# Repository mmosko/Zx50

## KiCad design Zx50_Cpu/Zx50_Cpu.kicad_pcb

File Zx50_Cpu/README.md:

# Zx50 CPU Card

## 1. Overview
This is the primary CPU board for the Zx50 8-slot passive backplane system. It hosts the Z80 microprocessor (running at 8 to 10 MHz) and acts as the master controller for the primary bus. 

Crucially, this board is designed to coexist with the **Zx50 Shadow Bus** architecture. It features a hardware-level "firewall" that allows a coprocessor (like a Pi Pico on the Bus Probe or Front Panel card) to request the bus via `~BUSRQ`. When the Z80 yields (`~BUSAK`), the CPU card instantly severs itself from the backplane, allowing the Pico to perform high-speed 40MHz DMA transfers without electrical contention.

## 2. Core Architecture & Logic Families

### The CPU
* **Z80 Microprocessor:** Zilog `Z84C00xxP` CMOS variant in a 40-pin DIP package. 

### The Transceiver Firewall (`74AHCT245`)
To drive the heavy capacitance of the 8-slot backplane, standard `74HC` logic is insufficient. This board uses **`74AHCT245`** octal bus transceivers (±8mA drive current) for all bus interfacing. 
To optimize PCB trace routing, a unified BOM of four '245s is used (rather than mixing in '244s). 
* **Convention:** "A-Ports" face the Z80; "B-Ports" face the Backplane.
* **Address Bus (x2):** `DIR` is hardwired to `+5V` (A -> B only).
* **Control Bus (x1):** `DIR` is hardwired to `+5V` (A -> B only). *(Note: The unused `A8` input on this buffer is tied to GND via a 10kΩ pull-up to prevent CMOS floating-gate oscillation).*
* **Data Bus (x1):** `DIR` is dynamically driven directly by the Z80's `~RD` pin. 
* **Isolation (`~OE`):** The `~OE` pins of all four transceivers are driven by an inverted `~BUSAK` signal. 

### Glue Logic (`74AHC1G14`)
A single "Little Logic" SOT-23-5 Schmitt-Trigger Inverter (`SN74AHC1G14DBVR` / Digi-Key: `296-1088-1-ND`) is used to invert the Z80's `~BUSAK` signal to correctly drive the active-low `~OE` pins of the transceiver wall.

## 3. Power-On Reset (POR) Subsystem
The Master Reset logic is completely handled by a **Microchip `MCP1318MT-46LE/OT`** Supervisor IC (SOT-23-5, Digi-Key: `MCP1318MT-46LE/OTCT-ND`). 

* **The Boot Delay:** It imposes a strict ~200ms delay on power-up. This guarantees the 1000µF backplane bulk capacitance is fully charged, the clock oscillators are stable, and the Pi Pico bootloaders on the peripheral cards have fully initialized before the Z80 takes its first step.
* **Voltage Threshold:** Trips at 4.6V to prevent brown-out corruption.
* **Open-Drain Output:** Safely shares the backplane's `~RESET` line with other cards that may pull the line low.
* **No Watchdog:** The `1318M` specifically omits the hardware watchdog timer (unlike the 1316M), preventing accidental Z80 reboots during extended Pi Pico DMA operations.
* **Local Button:** A right-angle tactile switch (`Omron B3F` / Digi-Key: `SW402-ND`) is wired to the `~MR` (Manual Reset) pin, providing perfect, capacitor-free hardware debouncing for bench testing.

## 4. Interfaces

* **J1 - Backplane:** Standard Zx50 80-pin Edge Connector.
* **J3 - Clock Mezzanine (2x5 Socket):** Receives `MCLK` (40MHz), `CLK` (10MHz ZCLK), and manages the async-latched `~STEP` signals from the Zx50 Clock Mezzanine module.
* **J4 - Front Panel (2x5 Header):** Mirrors the signals sent to the system Front Panel. Includes `RUN`, `~STEP`, `~RESET`, and `TX`/`RX` paths. The `~STEP` signal is routed down to the backplane's `AUX` pin (Pin 80) to coordinate with the Clock Mezzanine and Bus Probe.

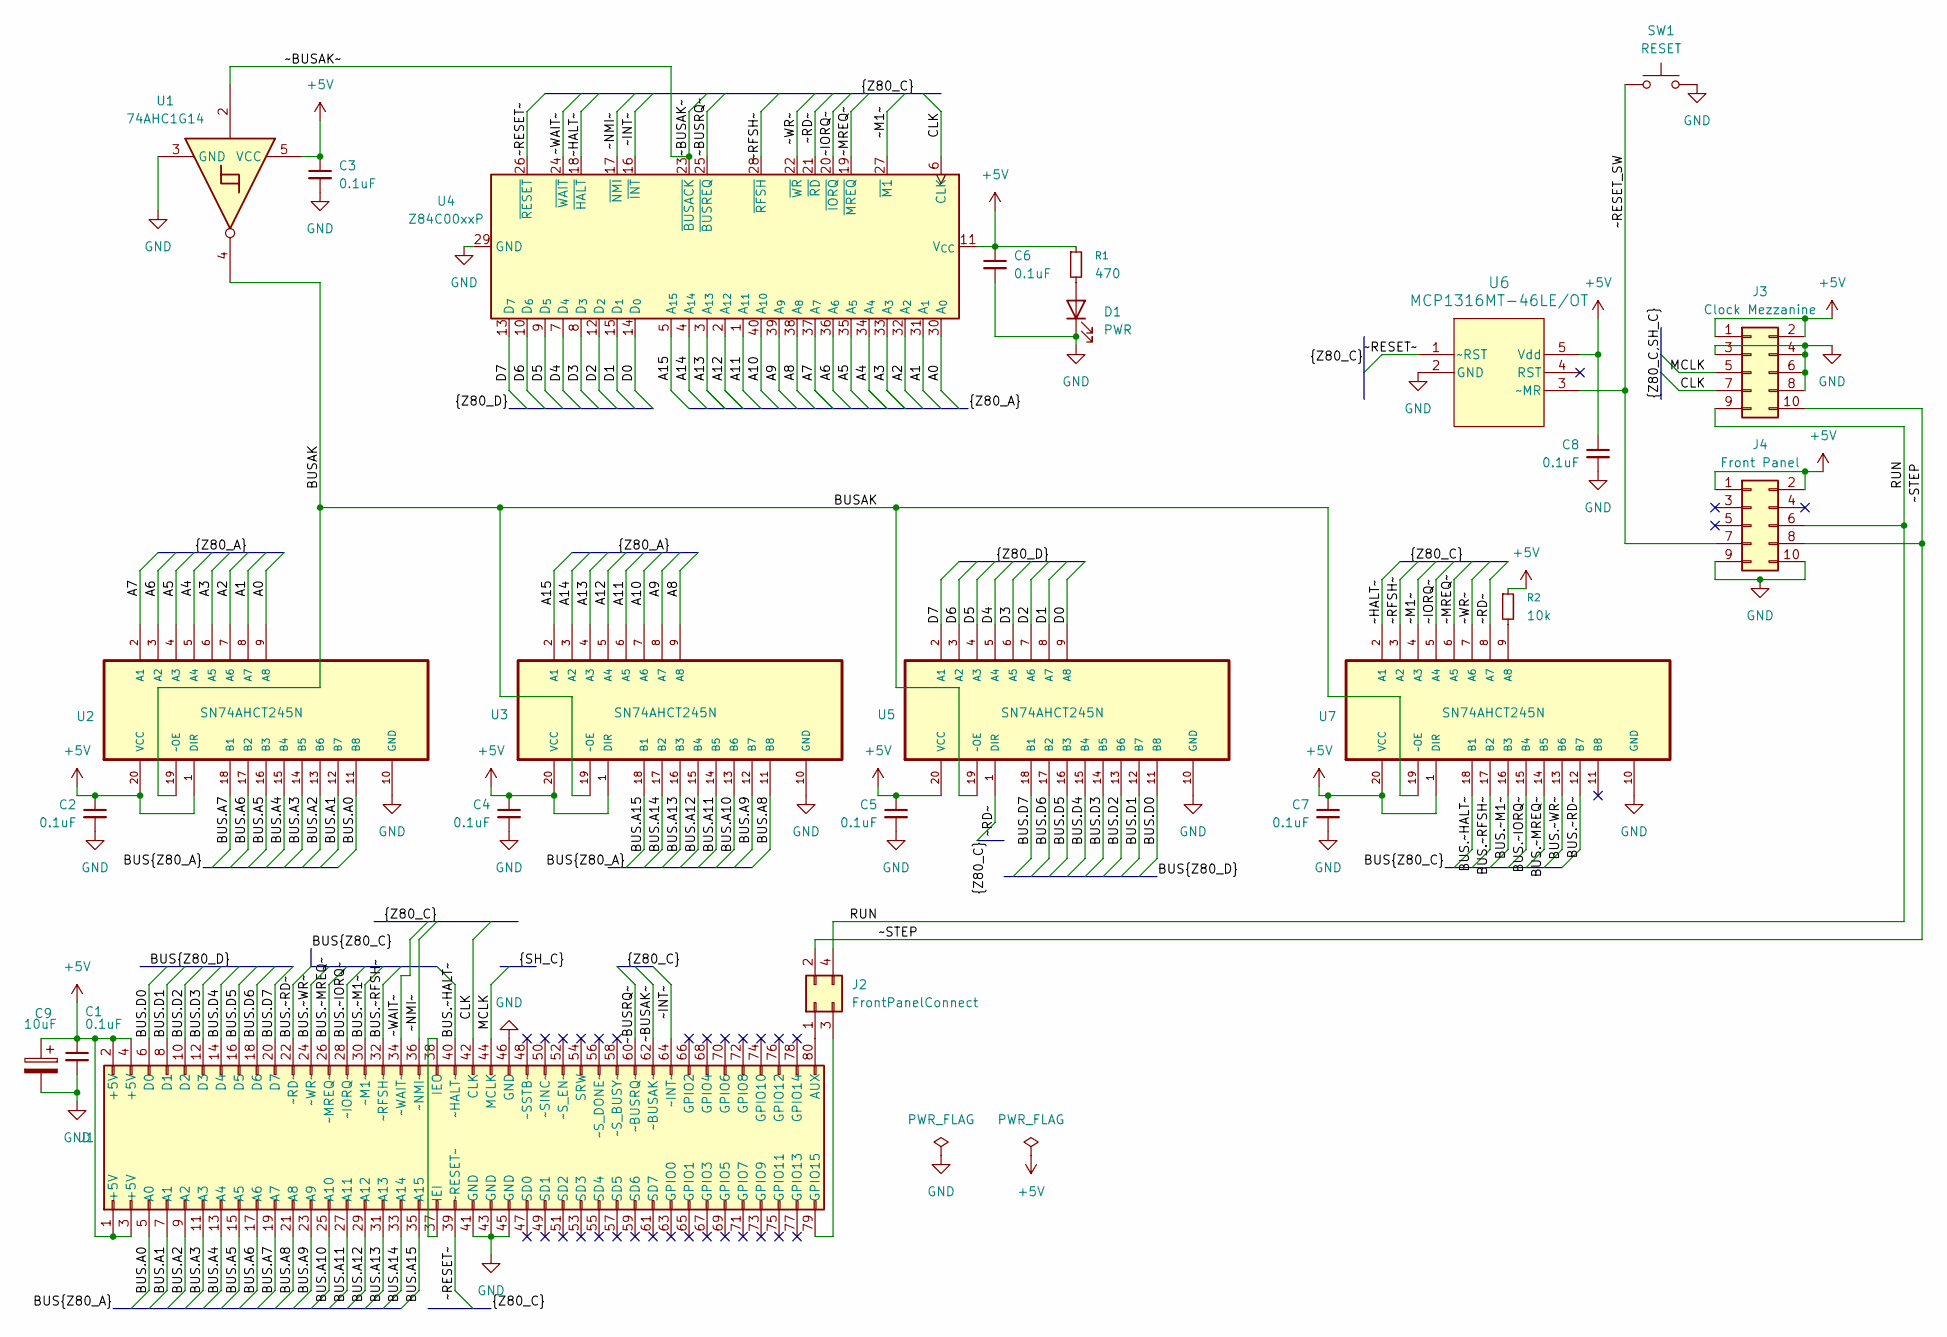
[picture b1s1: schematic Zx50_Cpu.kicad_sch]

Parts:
C1, C2, C3, C4, C5, C6, C7, C8: 0.1uF; C_Disc_D5.0mm_W2.5mm_P5.00mm; DigiKey_PN BC1101CT-ND
C9: 10uF; CP_Radial_Tantal_D5.0mm_P2.50mm; DigiKey_PN 399-1418-ND
D1: PWR; LED_D5.0mm
J1: Zx50_EdgeConnector; PinHeader_2x40_P2.54mm_Horizontal_Edge
J2: FrontPanelConnect; PinSocket_2x02_P2.54mm_Vertical
J3: Clock Mezzanine; PinSocket_2x05_P2.54mm_Horizontal
J4: Front Panel; IDC-Header_2x05_P2.54mm_Horizontal_Edge
R1: 470; R_Axial_DIN0207_L6.3mm_D2.5mm_P10.16mm_Horizontal
R2: 10k; R_Axial_DIN0207_L6.3mm_D2.5mm_P5.08mm_Vertical
SW1: RESET; SW_PUSH_6mm_H7.3mm; DigiKey_PN SW402-ND
U1: 74AHC1G14; SOT-23-5_HandSoldering; DigiKey_PN 296-1088-1-ND
U2, U3, U5, U7: SN74AHCT245N; DIP-20_W7.62mm_Socket; MPN SN74AHCT245N; Digikey_PN 296-1476-5-ND
U4: Z84C00xxP; DIP-40_W15.24mm
U6: MCP1316MT-46LE/OT; SOT-23-5_HandSoldering; Digikey_PN MCP1318MT-46LE/OTCT-ND

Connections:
+5V: C1.1, C2.1, C3.1, C4.1, C5.1, C6.1, C7.1, C8.1, C9.1, J1.1 (+5V), J1.2 (+5V), J1.3 (+5V), J1.4 (+5V), J3.1, J3.2, J4.1, J4.2, R1.1, R2.1, U1.5 (VCC), U2.1 (DIR), U2.20 (VCC), U3.1 (DIR), U3.20 (VCC), U4.11 (V_{CC}), U5.20 (VCC), U6.5 (Vdd), U7.1 (DIR), U7.20 (VCC)
/A0: U2.9 (A8), U4.30 (A_{0})
/A1: U2.8 (A7), U4.31 (A_{1})
/A2: U2.7 (A6), U4.32 (A_{2})
/A3: U2.6 (A5), U4.33 (A_{3})
/A4: U2.5 (A4), U4.34 (A_{4})
/A5: U2.4 (A3), U4.35 (A_{5})
/A6: U2.3 (A2), U4.36 (A_{6})
/A7: U2.2 (A1), U4.37 (A_{7})
/A8: U3.9 (A8), U4.38 (A_{8})
/A9: U3.8 (A7), U4.39 (A_{9})
/A10: U3.7 (A6), U4.40 (A_{10})
/A11: U3.6 (A5), U4.1 (A_{11})
/A12: U3.5 (A4), U4.2 (A_{12})
/A13: U3.4 (A3), U4.3 (A_{13})
/A14: U3.3 (A2), U4.4 (A_{14})
/A15: U3.2 (A1), U4.5 (A_{15})
/BUS.A0: J1.5 (A0), U2.11 (B8)
/BUS.A1: J1.7 (A1), U2.12 (B7)
/BUS.A2: J1.9 (A2), U2.13 (B6)
/BUS.A3: J1.11 (A3), U2.14 (B5)
/BUS.A4: J1.13 (A4), U2.15 (B4)
/BUS.A5: J1.15 (A5), U2.16 (B3)
/BUS.A6: J1.17 (A6), U2.17 (B2)
/BUS.A7: J1.19 (A7), U2.18 (B1)
/BUS.A8: J1.21 (A8), U3.11 (B8)
/BUS.A9: J1.23 (A9), U3.12 (B7)
/BUS.A10: J1.25 (A10), U3.13 (B6)
/BUS.A11: J1.27 (A11), U3.14 (B5)
/BUS.A12: J1.29 (A12), U3.15 (B4)
/BUS.A13: J1.31 (A13), U3.16 (B3)
/BUS.A14: J1.33 (A14), U3.17 (B2)
/BUS.A15: J1.35 (A15), U3.18 (B1)
/BUS.D0: J1.6 (D0), U5.11 (B8)
/BUS.D1: J1.8 (D1), U5.12 (B7)
/BUS.D2: J1.10 (D2), U5.13 (B6)
/BUS.D3: J1.12 (D3), U5.14 (B5)
/BUS.D4: J1.14 (D4), U5.15 (B4)
/BUS.D5: J1.16 (D5), U5.16 (B3)
/BUS.D6: J1.18 (D6), U5.17 (B2)
/BUS.D7: J1.20 (D7), U5.18 (B1)
/BUS.~HALT~: J1.40 (~HALT~), U7.18 (B1)
/BUS.~IORQ~: J1.28 (~IORQ~), U7.15 (B4)
/BUS.~M1~: J1.30 (~M1~), U7.16 (B3)
/BUS.~MREQ~: J1.26 (~MREQ~), U7.14 (B5)
/BUS.~RD~: J1.22 (~RD~), U7.12 (B7)
/BUS.~RFSH~: J1.32 (~RFSH~), U7.17 (B2)
/BUS.~WR~: J1.24 (~WR~), U7.13 (B6)
/BUSAK: U1.4, U2.19 (~OE), U3.19 (~OE), U5.19 (~OE), U7.19 (~OE)
/CLK: J1.42 (CLK), J3.7, U4.6 (CLK)
/D0: U4.14 (D_{0}), U5.9 (A8)
/D1: U4.15 (D_{1}), U5.8 (A7)
/D2: U4.12 (D_{2}), U5.7 (A6)
/D3: U4.8 (D_{3}), U5.6 (A5)
/D4: U4.7 (D_{4}), U5.5 (A4)
/D5: U4.9 (D_{5}), U5.4 (A3)
/D6: U4.10 (D_{6}), U5.3 (A2)
/D7: U4.13 (D_{7}), U5.2 (A1)
/MCLK: J1.44 (MCLK), J3.5
/RUN: J2.4, J3.9, J4.6
/~BUSAK~: J1.62 (~BUSAK~), U1.2, U4.23 (~BUSACK)
/~BUSRQ~: J1.60 (~BUSRQ~), U4.25 (~BUSREQ)
/~HALT~: U4.18 (~HALT), U7.2 (A1)
/~INT~: J1.64 (~INT~), U4.16 (~INT)
/~IORQ~: U4.20 (~IORQ), U7.5 (A4)
/~M1~: U4.27 (~M1), U7.4 (A3)
/~MREQ~: U4.19 (~MREQ), U7.6 (A5)
/~NMI~: J1.36 (~NMI~), U4.17 (~NMI)
/~RD~: U4.21 (~RD), U5.1 (DIR), U7.8 (A7)
/~RESET_SW: J4.7, SW1.1, U6.3 (~MR)
/~RESET~: J1.39 (~RESET~), U4.26 (~RESET), U6.1 (~RST)
/~RFSH~: U4.28 (~RFSH), U7.3 (A2)
/~STEP: J2.2, J3.10, J4.8
/~WAIT~: J1.34 (~WAIT~), U4.24 (~WAIT)
/~WR~: U4.22 (~WR), U7.7 (A6)
GND: C1.2, C2.2, C3.2, C4.2, C5.2, C6.2, C7.2, C8.2, C9.2, D1.1 (K), J1.41 (GND), J1.43 (GND), J1.45 (GND), J1.46 (GND), J3.3, J3.4, J3.6, J3.8, J4.9, J4.10, SW1.2, U1.3 (GND), U2.10 (GND), U3.10 (GND), U4.29 (GND), U5.10 (GND), U6.2 (GND), U7.10 (GND)
unnamed: D1.2 (A), R1.2
unnamed: J1.80 (AUX), J2.1
unnamed: J1.79 (GPIO15), J2.3
unnamed: J1.37 (IEI), J1.38 (IEO)
unnamed: R2.2, U7.9 (A8)

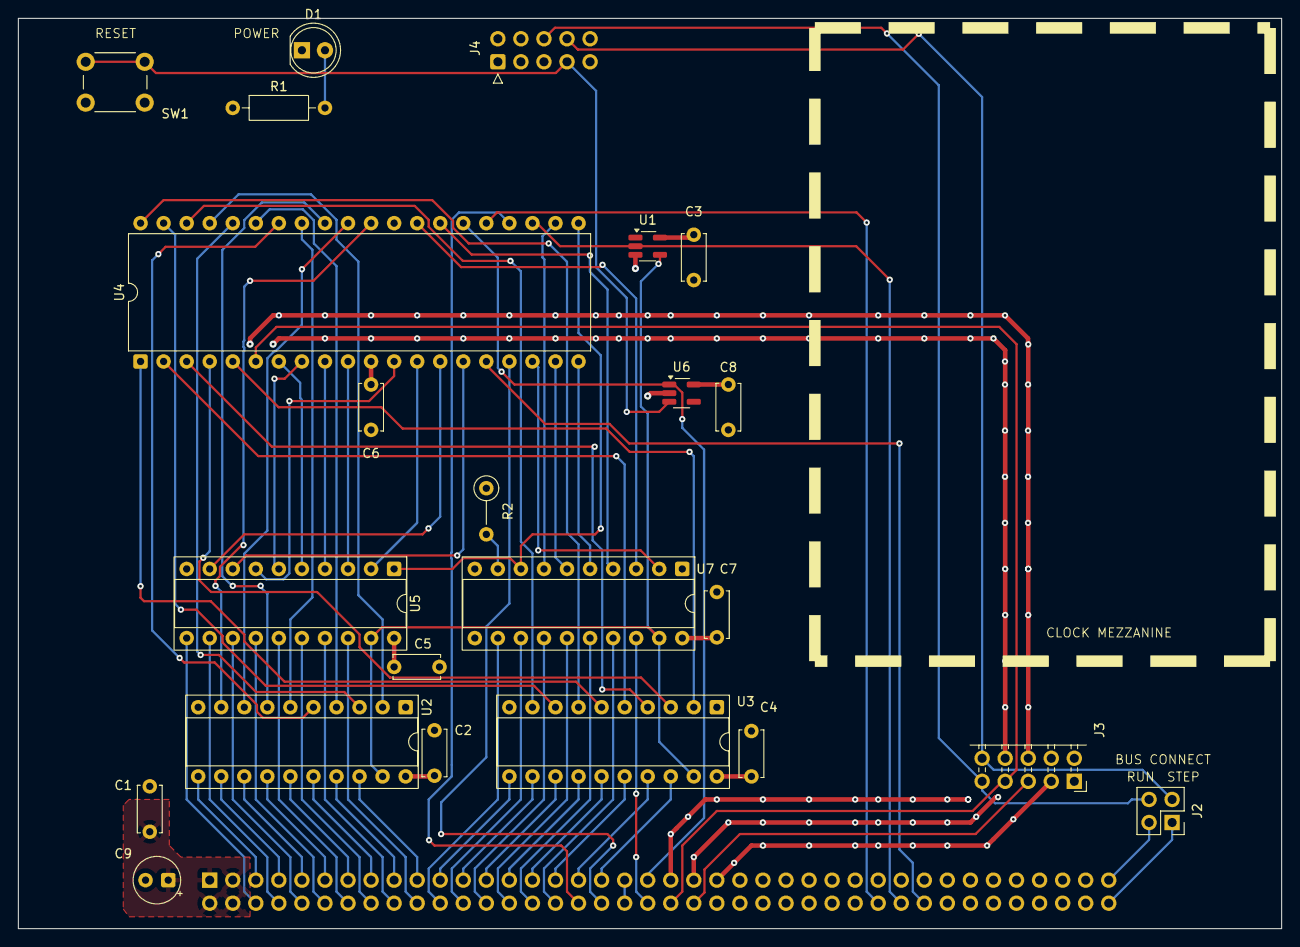
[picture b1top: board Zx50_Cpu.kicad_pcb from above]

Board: 4 copper layers, 139.2 x 100.3 mm, 24 parts (1 on the bottom side), 81 nets.

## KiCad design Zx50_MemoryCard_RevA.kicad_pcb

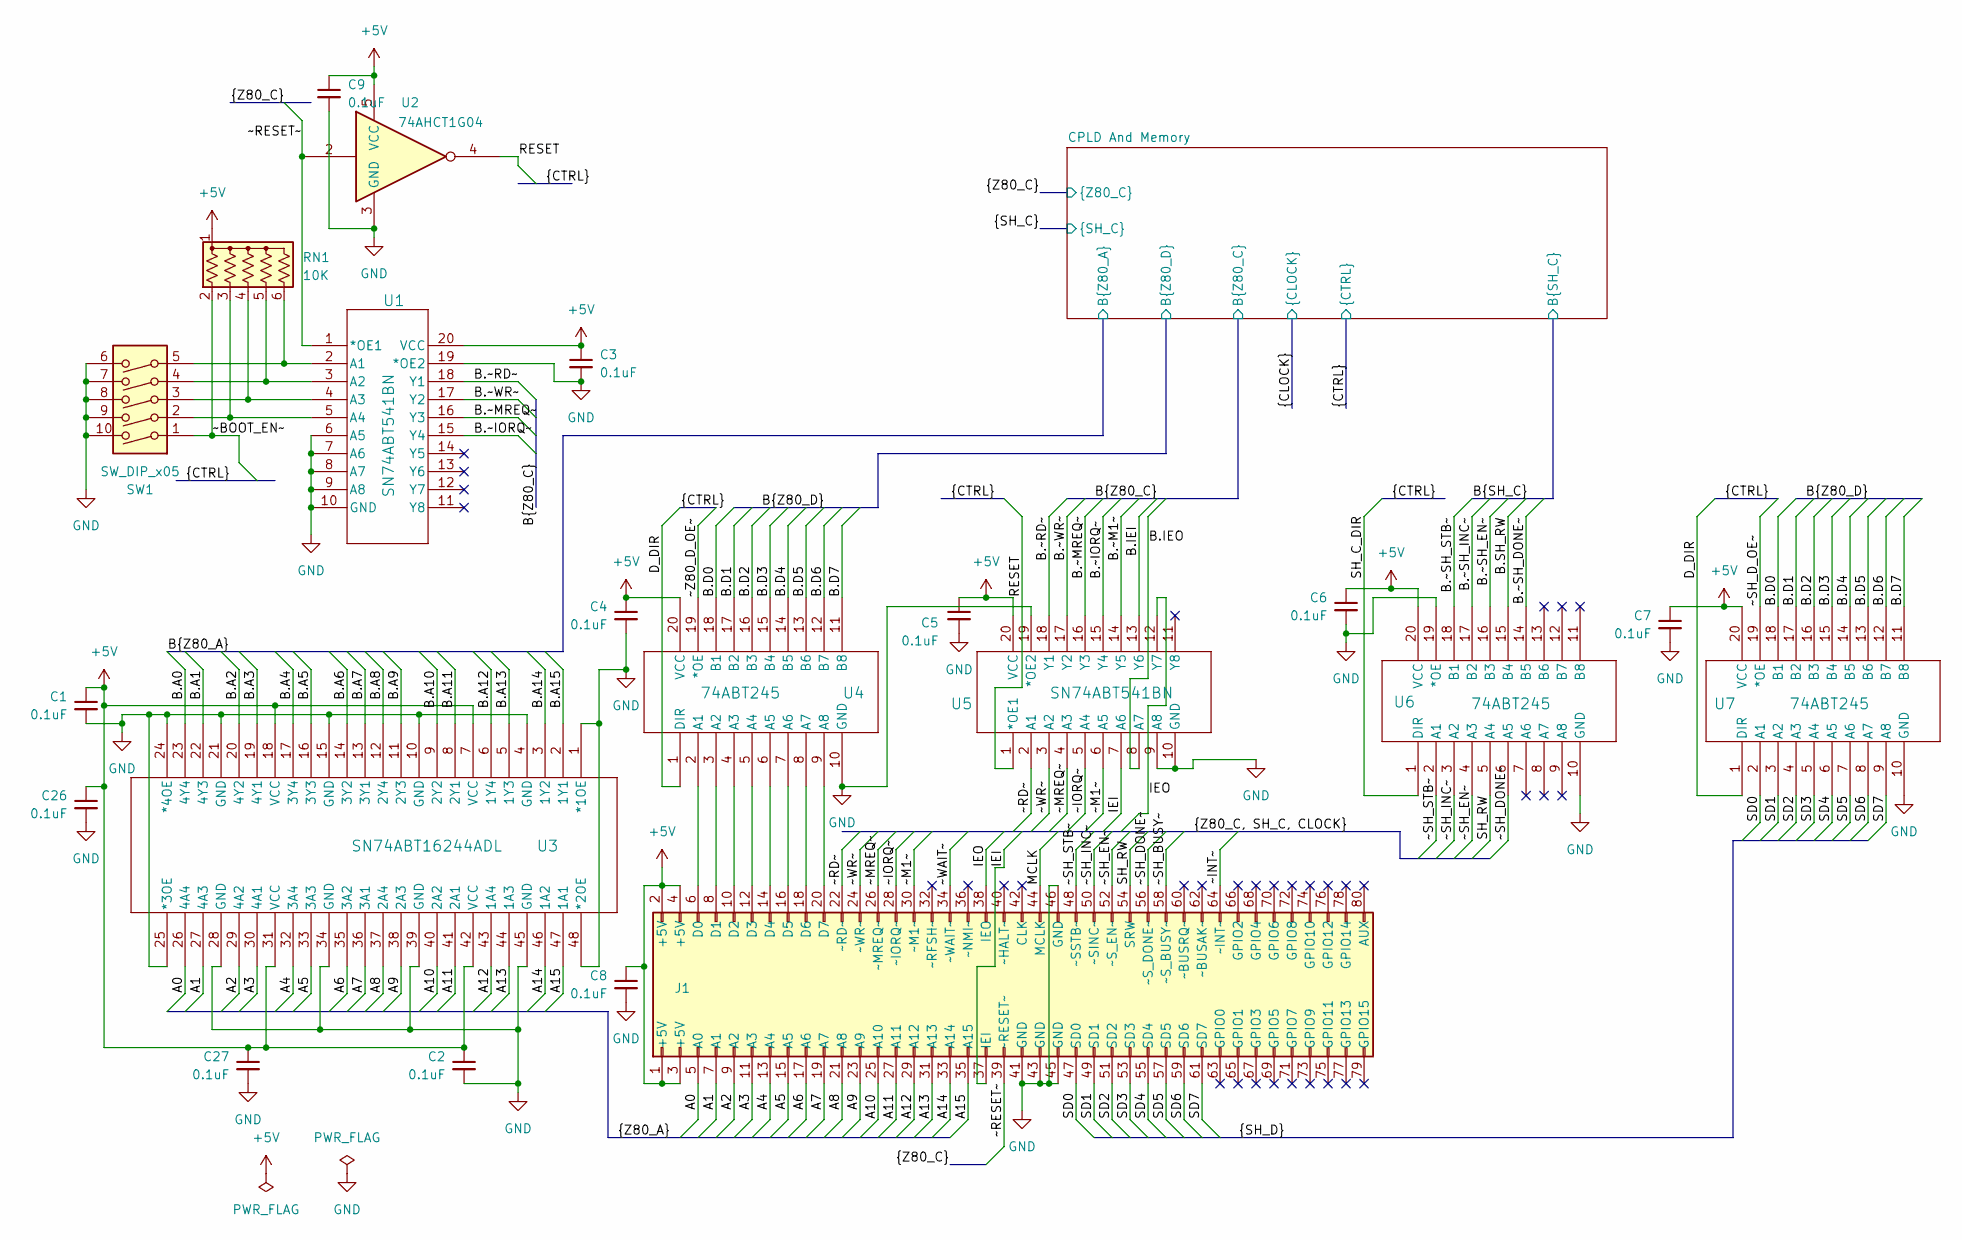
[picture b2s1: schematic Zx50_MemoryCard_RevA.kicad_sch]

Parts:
C1, C2, C3, C4, C5, C6, C7, C8, C9, C26, C27: 0.1uF; C_0603_1608Metric; LCSC C14663
J1: Zx50_EdgeConnector; PinSocket_2x40_P2.54mm_Horizontal_Edge
RN1: 10K; R_Array_SIP6
SW1: SW_DIP_x05; SW_DIP_SPSTx05_Slide_9.78x14.88mm_W7.62mm_P2.54mm
U1, U5: SN74ABT541BN; TSSOP-20_4.4x6.5mm_P0.65mm; LCSC C131956
U2: 74AHCT1G04; SOT-23-5; LCSC C52140419
U3: SN74ABT16244ADL; SSOP-48_7.5x15.9mm_P0.635mm; LCSC C2869608
U4, U6, U7: 74ABT245; SOIC-20W_7.5x12.8mm_P1.27mm; LCSC C1548132

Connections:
+5V: C1.1, C2.1, C3.1, C4.1, C5.1, C6.1, C7.1, C8.1, C9.1, C26.1, C27.1, J1.1 (+5V), J1.2 (+5V), J1.3 (+5V), J1.4 (+5V), RN1.1 (common), U1.20 (VCC), U2.5 (VCC), U3.7 (VCC), U3.18 (VCC), U3.31 (VCC), U3.42 (VCC), U4.20 (VCC), U5.20 (VCC), U6.20 (VCC), U7.20 (VCC); also elsewhere on the board
/A0: J1.5 (A0), U3.26 (4A4)
/A1: J1.7 (A1), U3.27 (4A3)
/A2: J1.9 (A2), U3.29 (4A2)
/A3: J1.11 (A3), U3.30 (4A1)
/A4: J1.13 (A4), U3.32 (3A4)
/A5: J1.15 (A5), U3.33 (3A3)
/A6: J1.17 (A6), U3.35 (3A2)
/A7: J1.19 (A7), U3.36 (3A1)
/A8: J1.21 (A8), U3.37 (2A4)
/A9: J1.23 (A9), U3.38 (2A3)
/A10: J1.25 (A10), U3.40 (2A2)
/A11: J1.27 (A11), U3.41 (2A1)
/A12: J1.29 (A12), U3.43 (1A4)
/A13: J1.31 (A13), U3.44 (1A3)
/A14: J1.33 (A14), U3.46 (1A2)
/A15: J1.35 (A15), U3.47 (1A1)
/B.A0: U3.23 (4Y4); also elsewhere on the board
/B.A1: U3.22 (4Y3); also elsewhere on the board
/B.A2: U3.20 (4Y2); also elsewhere on the board
/B.A3: U3.19 (4Y1); also elsewhere on the board
/B.A4: U3.17 (3Y4); also elsewhere on the board
/B.A5: U3.16 (3Y3); also elsewhere on the board
/B.A6: U3.14 (3Y2); also elsewhere on the board
/B.A7: U3.13 (3Y1); also elsewhere on the board
/B.A8: U3.12 (2Y4); also elsewhere on the board
/B.A9: U3.11 (2Y3); also elsewhere on the board
/B.A10: U3.9 (2Y2); also elsewhere on the board
/B.A11: U3.8 (2Y1); also elsewhere on the board
/B.A12: U3.6 (1Y4); also elsewhere on the board
/B.A13: U3.5 (1Y3); also elsewhere on the board
/B.A14: U3.3 (1Y2); also elsewhere on the board
/B.A15: U3.2 (1Y1); also elsewhere on the board
/B.D0: U4.18 (B1), U7.18 (B1); also elsewhere on the board
/B.D1: U4.17 (B2), U7.17 (B2); also elsewhere on the board
/B.D2: U4.16 (B3), U7.16 (B3); also elsewhere on the board
/B.D3: U4.15 (B4), U7.15 (B4); also elsewhere on the board
/B.D4: U4.14 (B5), U7.14 (B5); also elsewhere on the board
/B.D5: U4.13 (B6), U7.13 (B6); also elsewhere on the board
/B.D6: U4.12 (B7), U7.12 (B7); also elsewhere on the board
/B.D7: U4.11 (B8), U7.11 (B8); also elsewhere on the board
/B.IEI: U5.13 (Y6); also elsewhere on the board
/B.IEO: U5.8 (A7); also elsewhere on the board
/B.SH_RW: U6.15 (B4); also elsewhere on the board
/B.~IORQ~: U1.15 (Y4), U5.15 (Y4); also elsewhere on the board
/B.~M1~: U5.14 (Y5); also elsewhere on the board
/B.~MREQ~: U1.16 (Y3), U5.16 (Y3); also elsewhere on the board
/B.~RD~: U1.18 (Y1), U5.18 (Y1); also elsewhere on the board
/B.~SH_DONE~: U6.14 (B5); also elsewhere on the board
/B.~SH_EN~: U6.16 (B3); also elsewhere on the board
/B.~SH_INC~: U6.17 (B2); also elsewhere on the board
/B.~SH_STB~: U6.18 (B1); also elsewhere on the board
/B.~WR~: U1.17 (Y2), U5.17 (Y2); also elsewhere on the board
/D_DIR: U4.1 (DIR), U7.1 (DIR); also elsewhere on the board
/IEI: J1.37 (IEI), U5.7 (A6)
/IEO: J1.38 (IEO), U5.12 (Y7)
/MCLK: J1.44 (MCLK); also elsewhere on the board
/RESET: U2.4, U5.1 (*OE1)
/SD0: J1.47 (SD0), U7.2 (A1)
/SD1: J1.49 (SD1), U7.3 (A2)
/SD2: J1.51 (SD2), U7.4 (A3)
/SD3: J1.53 (SD3), U7.5 (A4)
/SD4: J1.55 (SD4), U7.6 (A5)
/SD5: J1.57 (SD5), U7.7 (A6)
/SD6: J1.59 (SD6), U7.8 (A7)
/SD7: J1.61 (SD7), U7.9 (A8)
/SH_C_DIR: U6.1 (DIR); also elsewhere on the board
/SH_RW: J1.54 (SRW), U6.5 (A4)
/~BOOT_EN~: RN1.2 (R1), SW1.1; also elsewhere on the board
/~INT~: J1.64 (~INT~); also elsewhere on the board
/~IORQ~: J1.28 (~IORQ~), U5.5 (A4)
/~M1~: J1.30 (~M1~), U5.6 (A5)
/~MREQ~: J1.26 (~MREQ~), U5.4 (A3)
/~RD~: J1.22 (~RD~), U5.2 (A1)
/~RESET~: J1.39 (~RESET~), U1.1 (*OE1), U2.2; also elsewhere on the board
/~SH_BUSY~: J1.58 (~S_BUSY~); also elsewhere on the board
/~SH_DONE~: J1.56 (~S_DONE~), U6.6 (A5)
/~SH_D_OE~: U7.19 (*OE); also elsewhere on the board
/~SH_EN~: J1.52 (~S_EN~), U6.4 (A3)
/~SH_INC~: J1.50 (~SINC~), U6.3 (A2)
/~SH_STB~: J1.48 (~SSTB~), U6.2 (A1)
/~WAIT~: J1.34 (~WAIT~); also elsewhere on the board
/~WR~: J1.24 (~WR~), U5.3 (A2)
/~Z80_D_OE~: U4.19 (*OE); also elsewhere on the board
GND: C1.2, C2.2, C3.2, C4.2, C5.2, C6.2, C7.2, C8.2, C9.2, C26.2, C27.2, J1.41 (GND), J1.43 (GND), J1.45 (GND), J1.46 (GND), SW1.6, SW1.7, SW1.8, SW1.9, SW1.10, U1.6 (A5), U1.7 (A6), U1.8 (A7), U1.9 (A8), U1.10 (GND), U1.19 (*OE2), U2.3 (GND), U3.1 (*1OE), U3.4 (GND), U3.10 (GND), U3.15 (GND), U3.21 (GND), U3.24 (*4OE), U3.25 (*3OE), U3.28 (GND), U3.34 (GND), U3.39 (GND), U3.45 (GND), U3.48 (*2OE), U4.10 (GND), U5.9 (A8), U5.10 (GND), U5.19 (*OE2), U6.10 (GND), U6.19 (*OE), U7.10 (GND); also elsewhere on the board
unnamed: J1.6 (D0), U4.2 (A1)
unnamed: J1.8 (D1), U4.3 (A2)
unnamed: J1.10 (D2), U4.4 (A3)
unnamed: J1.12 (D3), U4.5 (A4)
unnamed: J1.14 (D4), U4.6 (A5)
unnamed: J1.16 (D5), U4.7 (A6)
unnamed: J1.18 (D6), U4.8 (A7)
unnamed: J1.20 (D7), U4.9 (A8)
unnamed: RN1.3 (R2), SW1.2, U1.5 (A4)
unnamed: RN1.4 (R3), SW1.3, U1.4 (A3)
unnamed: RN1.5 (R4), SW1.4, U1.3 (A2)
unnamed: RN1.6 (R5), SW1.5, U1.2 (A1)

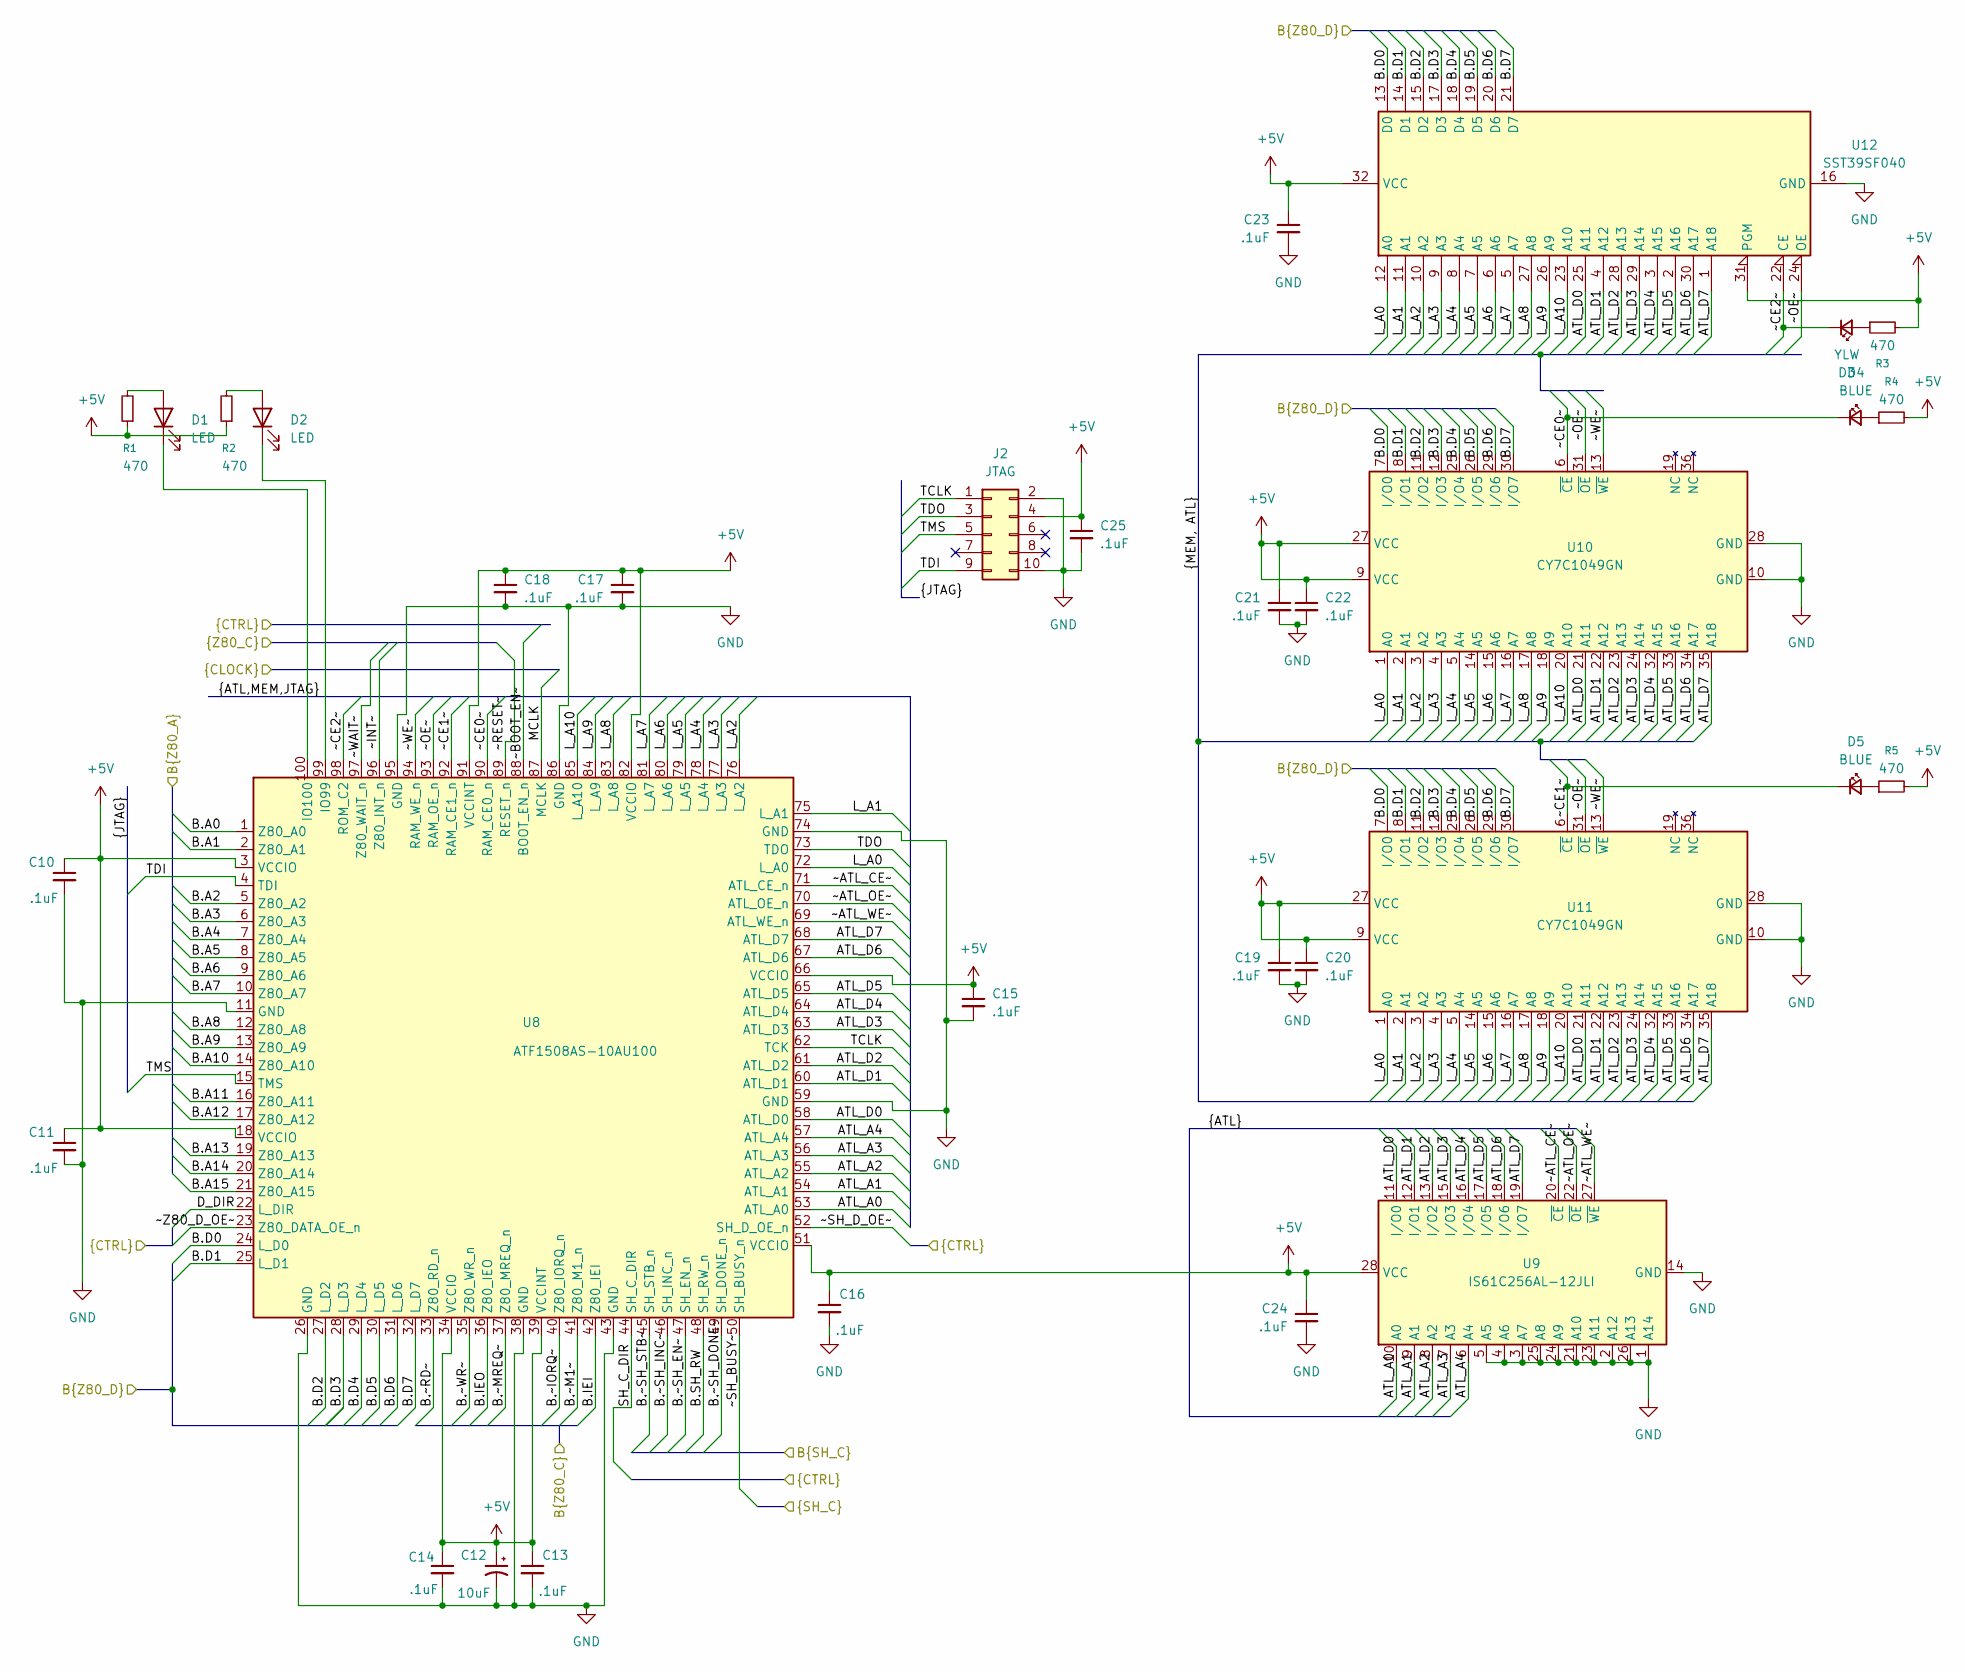
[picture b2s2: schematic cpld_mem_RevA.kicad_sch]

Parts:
C10, C11, C13, C14, C15, C16, C17, C18, C19, C20, C21, C22, C23, C24, C25: .1uF; C_0603_1608Metric; LCSC C14663
C12: 10uF; CP_Radial_Tantal_D5.0mm_P2.50mm
D1, D2: LED; LED_D3.0mm_Horizontal_O1.27mm_Z2.0mm
D3: YLW; LED_0805_2012Metric; LCSC C2296
D4, D5: BLUE; LED_0805_2012Metric; LCSC C2293
J2: JTAG; IDC-Header_2x05_P2.54mm_Vertical
R1, R2: 470; R_Axial_DIN0207_L6.3mm_D2.5mm_P7.62mm_Horizontal
R3, R4, R5: 470; R_0805_2012Metric; LCSC C17710
U8: ATF1508AS-10AU100; TQFP-100_14x14mm_P0.5mm; LCSC C31179
U9: IS61C256AL-12JLI; SOJ-28_7.62x18.415mm_P1.27mm; LCSC C2062861
U10, U11: CY7C1049GN; SOJ-36_10.16x23.495mm_P1.27mm; LCSC C2955765
U12: SST39SF040; DIP-32_W15.24mm_Socket

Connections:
+5V: C10.1, C11.1, C12.1, C13.1, C14.1, C15.1, C16.1, C17.1, C18.1, C19.1, C20.1, C21.1, C22.1, C23.1, C24.1, C25.1, J2.4, R1.1, R2.1, R3.2, R4.2, R5.2, U8.3 (VCCIO), U8.18 (VCCIO), U8.34 (VCCIO), U8.39 (VCCINT), U8.51 (VCCIO), U8.66 (VCCIO), U8.82 (VCCIO), U8.91 (VCCINT), U9.28 (VCC), U10.9 (VCC), U10.27 (VCC), U11.9 (VCC), U11.27 (VCC), U12.31 (PGM), U12.32 (VCC); also elsewhere on the board
/B.A0: U8.1 (Z80_A0); also elsewhere on the board
/B.A1: U8.2 (Z80_A1); also elsewhere on the board
/B.A2: U8.5 (Z80_A2); also elsewhere on the board
/B.A3: U8.6 (Z80_A3); also elsewhere on the board
/B.A4: U8.7 (Z80_A4); also elsewhere on the board
/B.A5: U8.8 (Z80_A5); also elsewhere on the board
/B.A6: U8.9 (Z80_A6); also elsewhere on the board
/B.A7: U8.10 (Z80_A7); also elsewhere on the board
/B.A8: U8.12 (Z80_A8); also elsewhere on the board
/B.A9: U8.13 (Z80_A9); also elsewhere on the board
/B.A10: U8.14 (Z80_A10); also elsewhere on the board
/B.A11: U8.16 (Z80_A11); also elsewhere on the board
/B.A12: U8.17 (Z80_A12); also elsewhere on the board
/B.A13: U8.19 (Z80_A13); also elsewhere on the board
/B.A14: U8.20 (Z80_A14); also elsewhere on the board
/B.A15: U8.21 (Z80_A15); also elsewhere on the board
/B.D0: U8.24 (L_D0), U10.7 (I/O0), U11.7 (I/O0), U12.13 (D0); also elsewhere on the board
/B.D1: U8.25 (L_D1), U10.8 (I/O1), U11.8 (I/O1), U12.14 (D1); also elsewhere on the board
/B.D2: U8.27 (L_D2), U10.11 (I/O2), U11.11 (I/O2), U12.15 (D2); also elsewhere on the board
/B.D3: U8.28 (L_D3), U10.12 (I/O3), U11.12 (I/O3), U12.17 (D3); also elsewhere on the board
/B.D4: U8.29 (L_D4), U10.25 (I/O4), U11.25 (I/O4), U12.18 (D4); also elsewhere on the board
/B.D5: U8.30 (L_D5), U10.26 (I/O5), U11.26 (I/O5), U12.19 (D5); also elsewhere on the board
/B.D6: U8.31 (L_D6), U10.29 (I/O6), U11.29 (I/O6), U12.20 (D6); also elsewhere on the board
/B.D7: U8.32 (L_D7), U10.30 (I/O7), U11.30 (I/O7), U12.21 (D7); also elsewhere on the board
/B.IEI: U8.42 (Z80_IEI); also elsewhere on the board
/B.IEO: U8.36 (Z80_IEO); also elsewhere on the board
/B.SH_RW: U8.48 (SH_RW_n); also elsewhere on the board
/B.~IORQ~: U8.40 (Z80_IORQ_n); also elsewhere on the board
/B.~M1~: U8.41 (Z80_M1_n); also elsewhere on the board
/B.~MREQ~: U8.37 (Z80_MREQ_n); also elsewhere on the board
/B.~RD~: U8.33 (Z80_RD_n); also elsewhere on the board
/B.~SH_DONE~: U8.49 (SH_DONE_n); also elsewhere on the board
/B.~SH_EN~: U8.47 (SH_EN_n); also elsewhere on the board
/B.~SH_INC~: U8.46 (SH_INC_n); also elsewhere on the board
/B.~SH_STB~: U8.45 (SH_STB_n); also elsewhere on the board
/B.~WR~: U8.35 (Z80_WR_n); also elsewhere on the board
/CPLD And Memory/ATL_A0: U8.53 (ATL_A0), U9.10 (A0)
/CPLD And Memory/ATL_A1: U8.54 (ATL_A1), U9.9 (A1)
/CPLD And Memory/ATL_A2: U8.55 (ATL_A2), U9.8 (A2)
/CPLD And Memory/ATL_A3: U8.56 (ATL_A3), U9.7 (A3)
/CPLD And Memory/ATL_A4: U8.57 (ATL_A4), U9.6 (A4)
/CPLD And Memory/ATL_D0: U8.58 (ATL_D0), U9.11 (I/O0), U10.21 (A11), U11.21 (A11), U12.25 (A11)
/CPLD And Memory/ATL_D1: U8.60 (ATL_D1), U9.12 (I/O1), U10.22 (A12), U11.22 (A12), U12.4 (A12)
/CPLD And Memory/ATL_D2: U8.61 (ATL_D2), U9.13 (I/O2), U10.23 (A13), U11.23 (A13), U12.28 (A13)
/CPLD And Memory/ATL_D3: U8.63 (ATL_D3), U9.15 (I/O3), U10.24 (A14), U11.24 (A14), U12.29 (A14)
/CPLD And Memory/ATL_D4: U8.64 (ATL_D4), U9.16 (I/O4), U10.32 (A15), U11.32 (A15), U12.3 (A15)
/CPLD And Memory/ATL_D5: U8.65 (ATL_D5), U9.17 (I/O5), U10.33 (A16), U11.33 (A16), U12.2 (A16)
/CPLD And Memory/ATL_D6: U8.67 (ATL_D6), U9.18 (I/O6), U10.34 (A17), U11.34 (A17), U12.30 (A17)
/CPLD And Memory/ATL_D7: U8.68 (ATL_D7), U9.19 (I/O7), U10.35 (A18), U11.35 (A18), U12.1 (A18)
/CPLD And Memory/L_A0: U8.72 (L_A0), U10.1 (A0), U11.1 (A0), U12.12 (A0)
/CPLD And Memory/L_A1: U8.75 (L_A1), U10.2 (A1), U11.2 (A1), U12.11 (A1)
/CPLD And Memory/L_A2: U8.76 (L_A2), U10.3 (A2), U11.3 (A2), U12.10 (A2)
/CPLD And Memory/L_A3: U8.77 (L_A3), U10.4 (A3), U11.4 (A3), U12.9 (A3)
/CPLD And Memory/L_A4: U8.78 (L_A4), U10.5 (A4), U11.5 (A4), U12.8 (A4)
/CPLD And Memory/L_A5: U8.79 (L_A5), U10.14 (A5), U11.14 (A5), U12.7 (A5)
/CPLD And Memory/L_A6: U8.80 (L_A6), U10.15 (A6), U11.15 (A6), U12.6 (A6)
/CPLD And Memory/L_A7: U8.81 (L_A7), U10.16 (A7), U11.16 (A7), U12.5 (A7)
/CPLD And Memory/L_A8: U8.83 (L_A8), U10.17 (A8), U11.17 (A8), U12.27 (A8)
/CPLD And Memory/L_A9: U8.84 (L_A9), U10.18 (A9), U11.18 (A9), U12.26 (A9)
/CPLD And Memory/L_A10: U8.85 (L_A10), U10.20 (A10), U11.20 (A10), U12.23 (A10)
/CPLD And Memory/TCLK: J2.1, U8.62 (TCK)
/CPLD And Memory/TDI: J2.9, U8.4 (TDI)
/CPLD And Memory/TDO: J2.3, U8.73 (TDO)
/CPLD And Memory/TMS: J2.5, U8.15 (TMS)
/CPLD And Memory/~ATL_CE~: U8.71 (ATL_CE_n), U9.20 (~CE)
/CPLD And Memory/~ATL_OE~: U8.70 (ATL_OE_n), U9.22 (~OE)
/CPLD And Memory/~ATL_WE~: U8.69 (ATL_WE_n), U9.27 (~WE)
/CPLD And Memory/~CE0~: D4.1 (K), U8.90 (RAM_CE0_n), U10.6 (~CE)
/CPLD And Memory/~CE1~: D5.1 (K), U8.92 (RAM_CE1_n), U11.6 (~CE)
/CPLD And Memory/~CE2~: D3.1 (K), U8.98 (ROM_C2), U12.22 (CE)
/CPLD And Memory/~OE~: U8.93 (RAM_OE_n), U10.31 (~OE), U11.31 (~OE), U12.24 (OE)
/CPLD And Memory/~WE~: U8.94 (RAM_WE_n), U10.13 (~WE), U11.13 (~WE)
/D_DIR: U8.22 (L_DIR); also elsewhere on the board
/MCLK: U8.87 (MCLK); also elsewhere on the board
/SH_C_DIR: U8.44 (SH_C_DIR); also elsewhere on the board
/~BOOT_EN~: U8.88 (BOOT_EN_n); also elsewhere on the board
/~INT~: U8.96 (Z80_INT_n); also elsewhere on the board
/~RESET~: U8.89 (RESET_n); also elsewhere on the board
/~SH_BUSY~: U8.50 (SH_BUSY_n); also elsewhere on the board
/~SH_D_OE~: U8.52 (SH_D_OE_n); also elsewhere on the board
/~WAIT~: U8.97 (Z80_WAIT_n); also elsewhere on the board
/~Z80_D_OE~: U8.23 (Z80_DATA_OE_n); also elsewhere on the board
GND: C10.2, C11.2, C12.2, C13.2, C14.2, C15.2, C16.2, C17.2, C18.2, C19.2, C20.2, C21.2, C22.2, C23.2, C24.2, C25.2, J2.2, J2.10, U8.11 (GND), U8.26 (GND), U8.38 (GND), U8.43 (GND), U8.59 (GND), U8.74 (GND), U8.86 (GND), U8.95 (GND), U9.1 (A14), U9.2 (A12), U9.3 (A7), U9.4 (A6), U9.5 (A5), U9.14 (GND), U9.21 (A10), U9.23 (A11), U9.24 (A9), U9.25 (A8), U9.26 (A13), U10.10 (GND), U10.28 (GND), U11.10 (GND), U11.28 (GND), U12.16 (GND); also elsewhere on the board
unnamed: D1.2 (A), R1.2
unnamed: D1.1 (K), U8.100 (IO100)
unnamed: D2.2 (A), R2.2
unnamed: D2.1 (K), U8.99 (IO99)
unnamed: D3.2 (A), R3.1
unnamed: D4.2 (A), R4.1
unnamed: D5.2 (A), R5.1

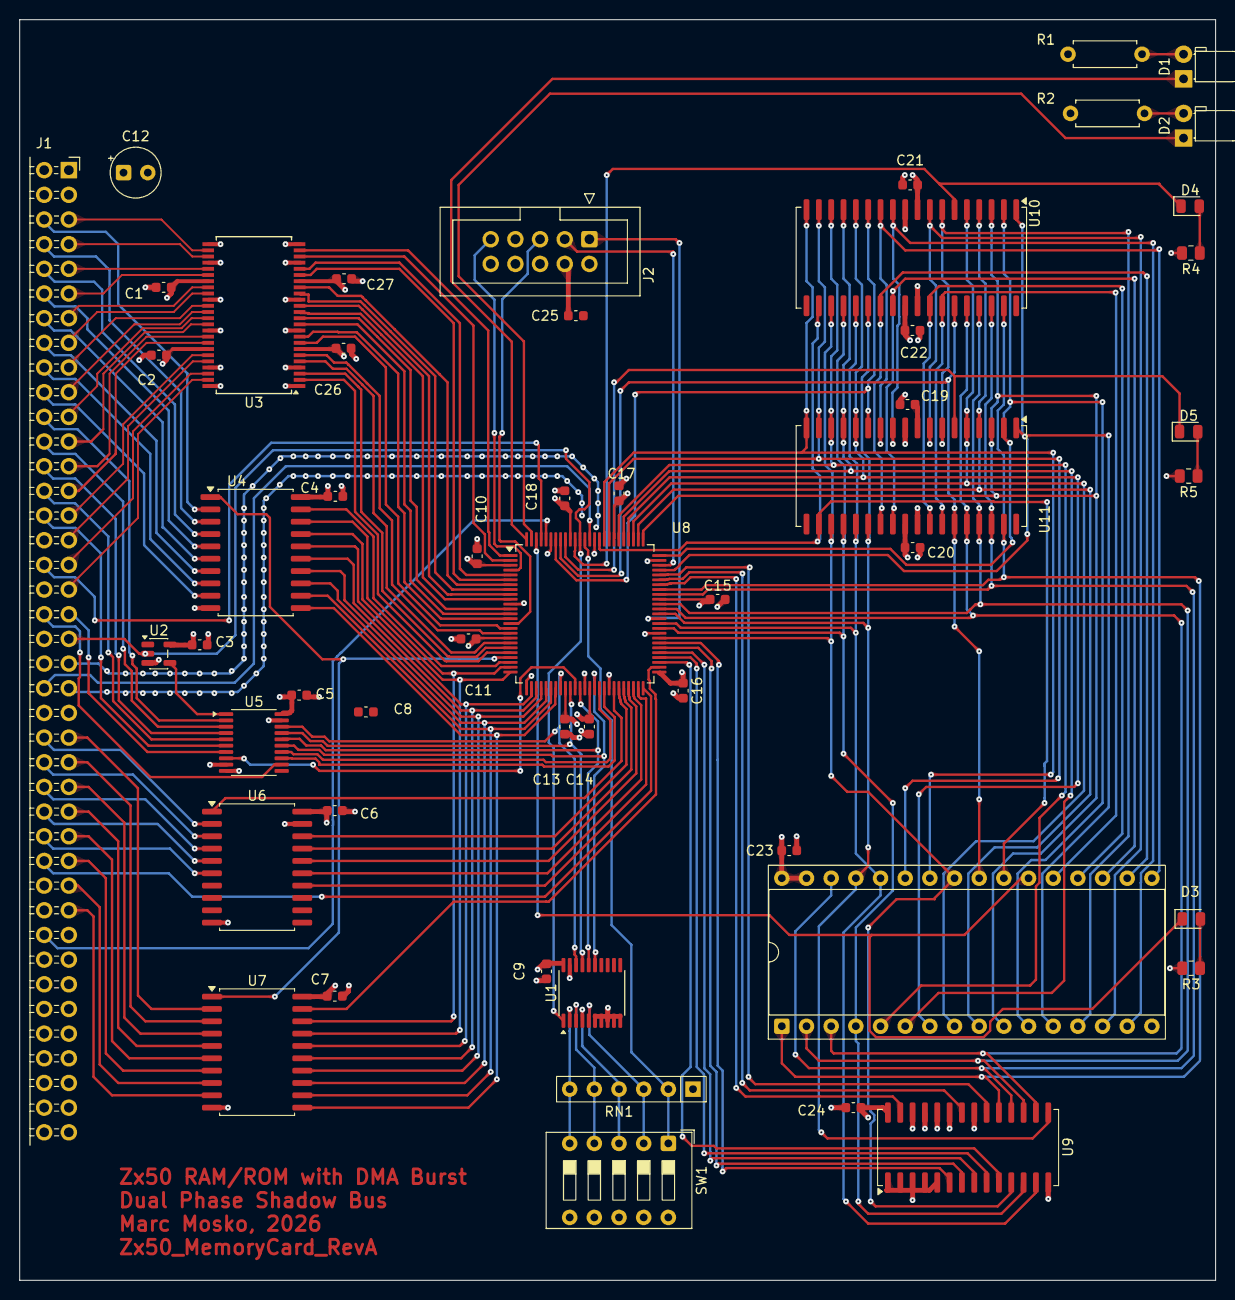
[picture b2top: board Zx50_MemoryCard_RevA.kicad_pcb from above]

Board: 4 copper layers, 123.1 x 129.8 mm, 53 parts (0 on the bottom side), 140 nets.
